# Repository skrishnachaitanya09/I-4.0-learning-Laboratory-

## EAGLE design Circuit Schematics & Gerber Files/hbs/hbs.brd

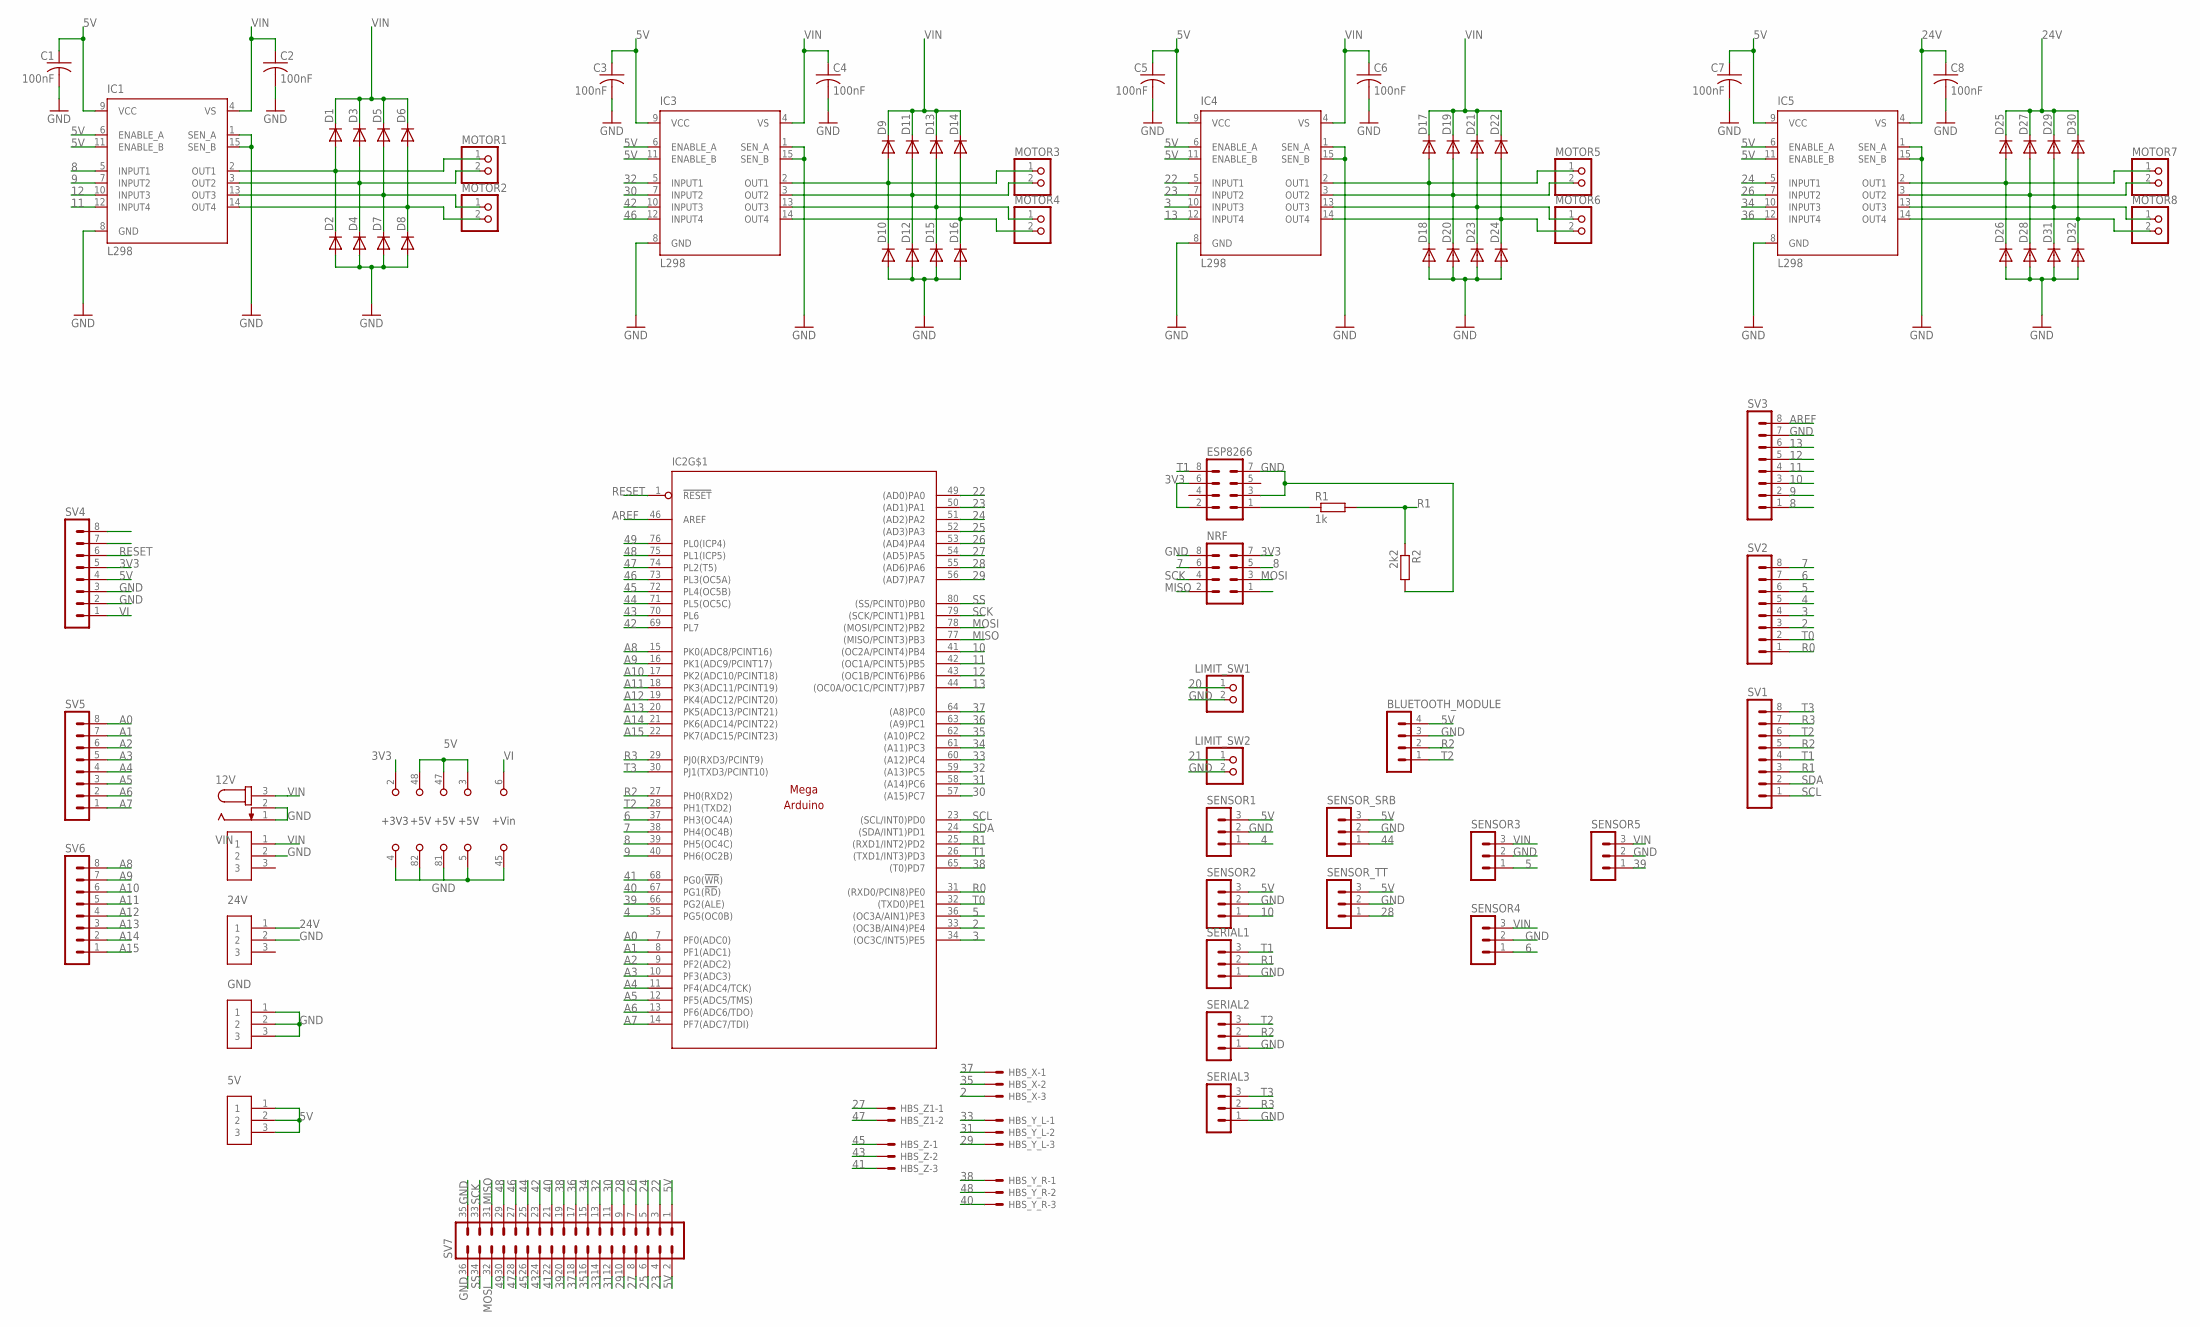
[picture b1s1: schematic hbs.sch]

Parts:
5V, 24V: 691311500003; TERMINALBLOCK_PLUGGABLE-3-5.08MM
12V: JACK-PLUG0; SPC4077
BLUETOOTH_MODULE: MA04-1
C1, C2, C3, C4, C5, C6, C7, C8: 100nF; C050-024X044
D1, D2, D3, D4, D5, D6, D7, D8, D9, D10, D11, D12, D13, D14, D15, D16, D17, D18, D19, D20, D21, D22, D23, D24, D25, D26, D27, D28, D29, D30, D31, D32: DIODE-D-5; D-5
ESP8266: MA04-2
GND: 691311500003; TERMINALBLOCK_PLUGGABLE-3-5.08MM
HBS_X: JST-XH-03-PIN-LONG-PAD; JST-XH-03-PACKAGE-LONG-PAD
HBS_Y_L: JST-XH-03-PIN-LONG-PAD; JST-XH-03-PACKAGE-LONG-PAD
HBS_Y_R: JST-XH-03-PIN-LONG-PAD; JST-XH-03-PACKAGE-LONG-PAD
HBS_Z: JST-XH-03-PIN-LONG-PAD; JST-XH-03-PACKAGE-LONG-PAD
HBS_Z1: JST-XH-02-PIN-LONG-PAD; JST-XH-02-PACKAGE-LONG-PAD
IC1, IC3, IC4, IC5: L298; MULTIWATT-15
IC2: MEGAARDUINO_21; MEGA_ARDUINO_1
LIMIT_SW1, LIMIT_SW2: PINHD-1X2; 1X02
MOTOR1, MOTOR2, MOTOR3, MOTOR4, MOTOR5, MOTOR6, MOTOR7, MOTOR8: PINHD-1X2; 1X02
NRF: MA04-2
R1: 1k; 0204/7
R2: 2k2; 0204/7
SENSOR1, SENSOR2, SENSOR3, SENSOR4, SENSOR5: MA03-1
SENSOR_SRB: MA03-1
SENSOR_TT: MA03-1
SERIAL1, SERIAL2, SERIAL3: MA03-1
SV1, SV2, SV3, SV4, SV5, SV6: MA08-1
SV7: MA18-2
VIN: 691311500003; TERMINALBLOCK_PLUGGABLE-3-5.08MM

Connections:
2: HBS_X.3, IC2.33 ((OC3B/AIN4)PE4), SV2.3
3: IC2.34 ((OC3C/INT5)PE5), IC4.10 (INPUT3), SV2.4
3V3: ESP8266.2, ESP8266.6, IC2.2 (+3V3), NRF.7, SV4.5
4: IC2.35 (PG5(OC0B)), SENSOR1.1, SV2.5
5: IC2.36 ((OC3A/AIN1)PE3), SENSOR3.1, SV2.6
5V: 5V.1, 5V.2, 5V.3, BLUETOOTH_MODULE.4, C1.1, C3.1, C5.1, C7.1, IC1.6 (ENABLE_A), IC1.9 (VCC), IC1.11 (ENABLE_B), IC2.3 (+5V), IC2.47 (+5V), IC2.48 (+5V), IC3.6 (ENABLE_A), IC3.9 (VCC), IC3.11 (ENABLE_B), IC4.6 (ENABLE_A), IC4.9 (VCC), IC4.11 (ENABLE_B), IC5.6 (ENABLE_A), IC5.9 (VCC), IC5.11 (ENABLE_B), SENSOR1.3, SENSOR2.3, SENSOR_SRB.3, SENSOR_TT.3, SV4.4, SV7.1, SV7.2
6: IC2.37 (PH3(OC4A)), SENSOR4.1, SV2.7
7: IC2.38 (PH4(OC4B)), NRF.6, SV2.8
8: IC1.5 (INPUT1), IC2.39 (PH5(OC4C)), NRF.5, SV3.1
9: IC1.7 (INPUT2), IC2.40 (PH6(OC2B)), SV3.2
10: IC2.41 ((OC2A/PCINT4)PB4), SENSOR2.1, SV3.3
11: IC1.12 (INPUT4), IC2.42 ((OC1A/PCINT5)PB5), SV3.4
12: IC1.10 (INPUT3), IC2.43 ((OC1B/PCINT6)PB6), SV3.5
13: IC2.44 ((OC0A/OC1C/PCINT7)PB7), IC4.12 (INPUT4), SV3.6
20: LIMIT_SW1.1
21: LIMIT_SW2.1
22: IC2.49 ((AD0)PA0), IC4.5 (INPUT1), SV7.3
23: IC2.50 ((AD1)PA1), IC4.7 (INPUT2), SV7.4
24: IC2.51 ((AD2)PA2), IC5.5 (INPUT1), SV7.5
24V: 24V.1, C8.1, D25.C, D27.C, D29.C, D30.C, IC5.4 (VS)
25: IC2.52 ((AD3)PA3), SV7.6
26: IC2.53 ((AD4)PA4), IC5.7 (INPUT2), SV7.7
27: HBS_Z1.1, IC2.54 ((AD5)PA5), SV7.8
28: IC2.55 ((AD6)PA6), SENSOR_TT.1, SV7.9
29: HBS_Y_L.3, IC2.56 ((AD7)PA7), SV7.10
30: IC2.57 ((A15)PC7), IC3.7 (INPUT2), SV7.11
31: HBS_Y_L.2, IC2.58 ((A14)PC6), SV7.12
32: IC2.59 ((A13)PC5), IC3.5 (INPUT1), SV7.13
33: HBS_Y_L.1, IC2.60 ((A12)PC4), SV7.14
34: IC2.61 ((A11)PC3), IC5.10 (INPUT3), SV7.15
35: HBS_X.2, IC2.62 ((A10)PC2), SV7.16
36: IC2.63 ((A9)PC1), IC5.12 (INPUT4), SV7.17
37: HBS_X.1, IC2.64 ((A8)PC0), SV7.18
38: HBS_Y_R.1, IC2.65 ((T0)PD7), SV7.19
39: IC2.66 (PG2(ALE)), SENSOR5.1, SV7.20
40: HBS_Y_R.3, IC2.67 (PG1(!RD!)), SV7.21
41: HBS_Z.3, IC2.68 (PG0(!WR!)), SV7.22
42: IC2.69 (PL7), IC3.10 (INPUT3), SV7.23
43: HBS_Z.2, IC2.70 (PL6), SV7.24
44: IC2.71 (PL5(OC5C)), SENSOR_SRB.1, SV7.25
45: HBS_Z.1, IC2.72 (PL4(OC5B)), SV7.26
46: IC2.73 (PL3(OC5A)), IC3.12 (INPUT4), SV7.27
47: HBS_Z1.2, IC2.74 (PL2(T5)), SV7.28
48: HBS_Y_R.2, IC2.75 (PL1(ICP5)), SV7.29
49: IC2.76 (PL0(ICP4)), SV7.30
A0: IC2.7 (PF0(ADC0)), SV5.8
A1: IC2.8 (PF1(ADC1)), SV5.7
A2: IC2.9 (PF2(ADC2)), SV5.6
A3: IC2.10 (PF3(ADC3)), SV5.5
A4: IC2.11 (PF4(ADC4/TCK)), SV5.4
A5: IC2.12 (PF5(ADC5/TMS)), SV5.3
A6: IC2.13 (PF6(ADC6/TDO)), SV5.2
A7: IC2.14 (PF7(ADC7/TDI)), SV5.1
A8: IC2.15 (PK0(ADC8/PCINT16)), SV6.8
A9: IC2.16 (PK1(ADC9/PCINT17)), SV6.7
A10: IC2.17 (PK2(ADC10/PCINT18)), SV6.6
A11: IC2.18 (PK3(ADC11/PCINT19)), SV6.5
A12: IC2.19 (PK4(ADC12/PCINT20)), SV6.4
A13: IC2.20 (PK5(ADC13/PCINT21)), SV6.3
A14: IC2.21 (PK6(ADC14/PCINT22)), SV6.2
A15: IC2.22 (PK7(ADC15/PCINT23)), SV6.1
AREF: IC2.46 (AREF), SV3.8
GND: 12V.1, 12V.2, 24V.2, BLUETOOTH_MODULE.3, C1.2, C2.2, C3.2, C4.2, C5.2, C6.2, C7.2, C8.2, D2.A, D4.A, D7.A, D8.A, D10.A, D12.A, D15.A, D16.A, D18.A, D20.A, D23.A, D24.A, D26.A, D28.A, D31.A, D32.A, ESP8266.3, ESP8266.7, GND.1, GND.2, GND.3, IC1.1 (SEN_A), IC1.8 (GND), IC1.15 (SEN_B), IC2.4 (GND), IC2.5 (GND), IC2.45 (GND), IC2.81 (GND), IC2.82 (GND), IC3.1 (SEN_A), IC3.8 (GND), IC3.15 (SEN_B), IC4.1 (SEN_A), IC4.8 (GND), IC4.15 (SEN_B), IC5.1 (SEN_A), IC5.8 (GND), IC5.15 (SEN_B), LIMIT_SW1.2, LIMIT_SW2.2, NRF.8, R2.2, SENSOR1.2, SENSOR2.2, SENSOR3.2, SENSOR4.2, SENSOR5.2, SENSOR_SRB.2, SENSOR_TT.2, SERIAL1.1, SERIAL2.1, SERIAL3.1, SV3.7, SV4.2, SV4.3, SV7.35, SV7.36, VIN.2
MISO: IC2.77 ((MISO/PCINT3)PB3), NRF.2, SV7.31
MOSI: IC2.78 ((MOSI/PCINT2)PB2), NRF.3, SV7.32
unnamed: D1.A, D2.C, IC1.2 (OUT1), MOTOR1.1
unnamed: D3.A, D4.C, IC1.3 (OUT2), MOTOR1.2
unnamed: D6.A, D8.C, IC1.14 (OUT4), MOTOR2.2
unnamed: D5.A, D7.C, IC1.13 (OUT3), MOTOR2.1
unnamed: ESP8266.1, R1.1
unnamed: D9.A, D10.C, IC3.2 (OUT1), MOTOR3.1
unnamed: D11.A, D12.C, IC3.3 (OUT2), MOTOR3.2
unnamed: D14.A, D16.C, IC3.14 (OUT4), MOTOR4.2
unnamed: D13.A, D15.C, IC3.13 (OUT3), MOTOR4.1
unnamed: D17.A, D18.C, IC4.2 (OUT1), MOTOR5.1
unnamed: D19.A, D20.C, IC4.3 (OUT2), MOTOR5.2
unnamed: D22.A, D24.C, IC4.14 (OUT4), MOTOR6.2
unnamed: D21.A, D23.C, IC4.13 (OUT3), MOTOR6.1
unnamed: D25.A, D26.C, IC5.2 (OUT1), MOTOR7.1
unnamed: D27.A, D28.C, IC5.3 (OUT2), MOTOR7.2
unnamed: D30.A, D32.C, IC5.14 (OUT4), MOTOR8.2
unnamed: D29.A, D31.C, IC5.13 (OUT3), MOTOR8.1
R0: IC2.31 ((RXD0/PCIN8)PE0), SV2.1
R1: IC2.25 ((RXD1/INT2)PD2), R1.2, R2.1, SERIAL1.2, SV1.3
R2: BLUETOOTH_MODULE.2, IC2.27 (PH0(RXD2)), SERIAL2.2, SV1.5
R3: IC2.29 (PJ0(RXD3/PCINT9)), SERIAL3.2, SV1.7
RESET: IC2.1 (!RESET), SV4.6
SCK: IC2.79 ((SCK/PCINT1)PB1), NRF.4, SV7.33
SCL: IC2.23 ((SCL/INT0)PD0), SV1.1
SDA: IC2.24 ((SDA/INT1)PD1), SV1.2
SS: IC2.80 ((SS/PCINT0)PB0), SV7.34
T0: IC2.32 ((TXD0)PE1), SV2.2
T1: ESP8266.8, IC2.26 ((TXD1/INT3)PD3), SERIAL1.3, SV1.4
T2: BLUETOOTH_MODULE.1, IC2.28 (PH1(TXD2)), SERIAL2.3, SV1.6
T3: IC2.30 (PJ1(TXD3/PCINT10)), SERIAL3.3, SV1.8
VI: IC2.6 (+VIN), SV4.1
VIN: 12V.3, C2.1, C4.1, C6.1, D1.C, D3.C, D5.C, D6.C, D9.C, D11.C, D13.C, D14.C, D17.C, D19.C, D21.C, D22.C, IC1.4 (VS), IC3.4 (VS), IC4.4 (VS), SENSOR3.3, SENSOR4.3, SENSOR5.3, VIN.1

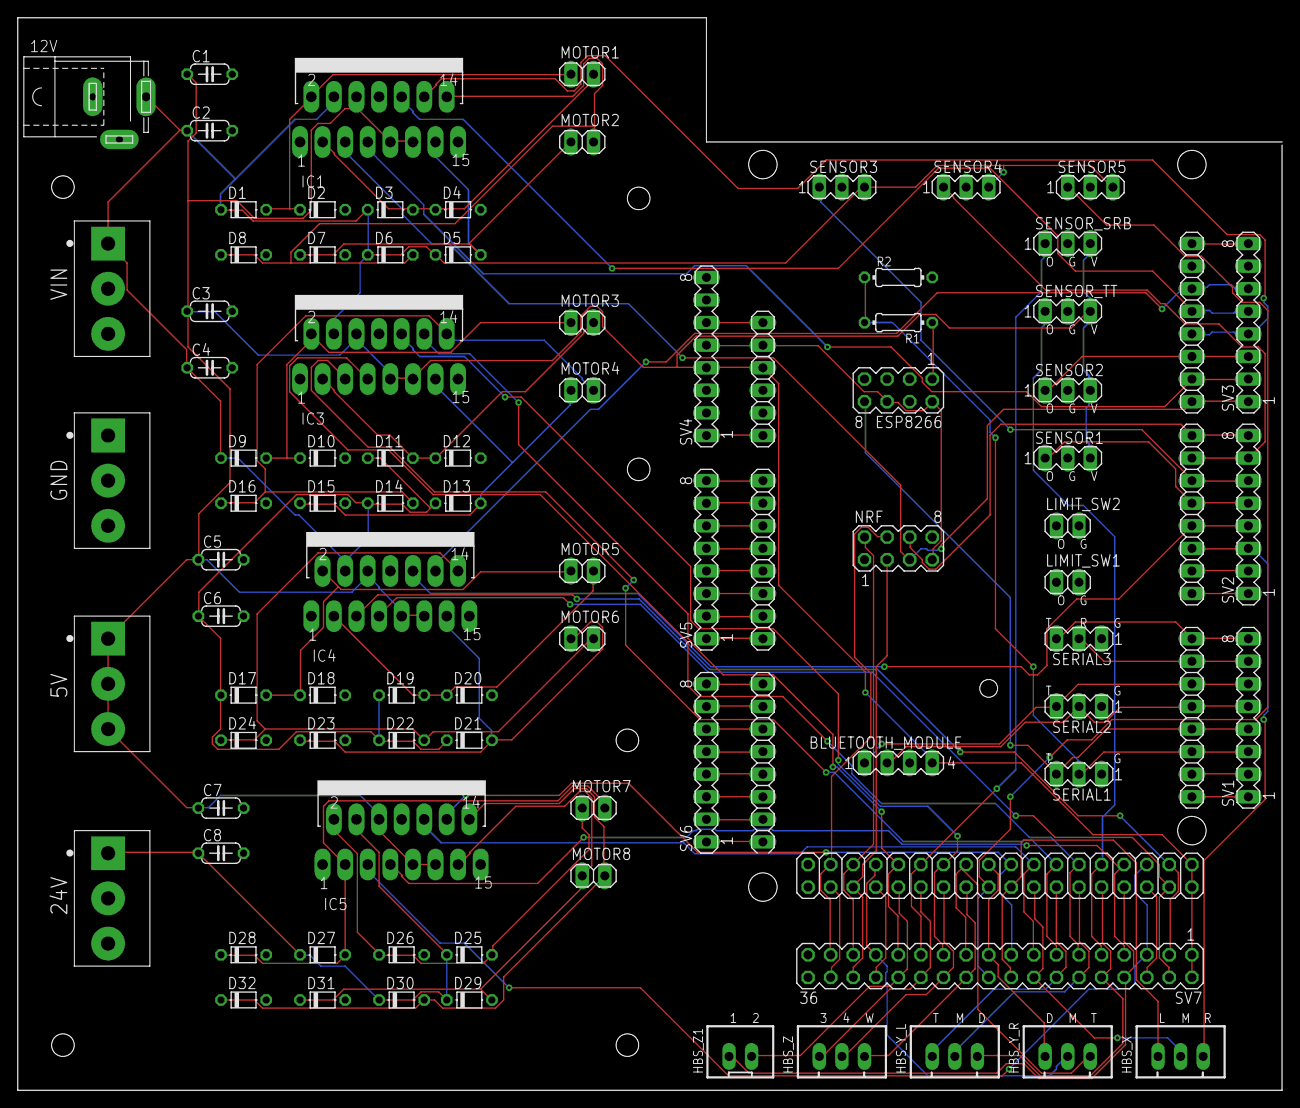
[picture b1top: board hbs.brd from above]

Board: 2 copper layers, 142.2 x 120.7 mm, 87 parts (0 on the bottom side), 95 nets.

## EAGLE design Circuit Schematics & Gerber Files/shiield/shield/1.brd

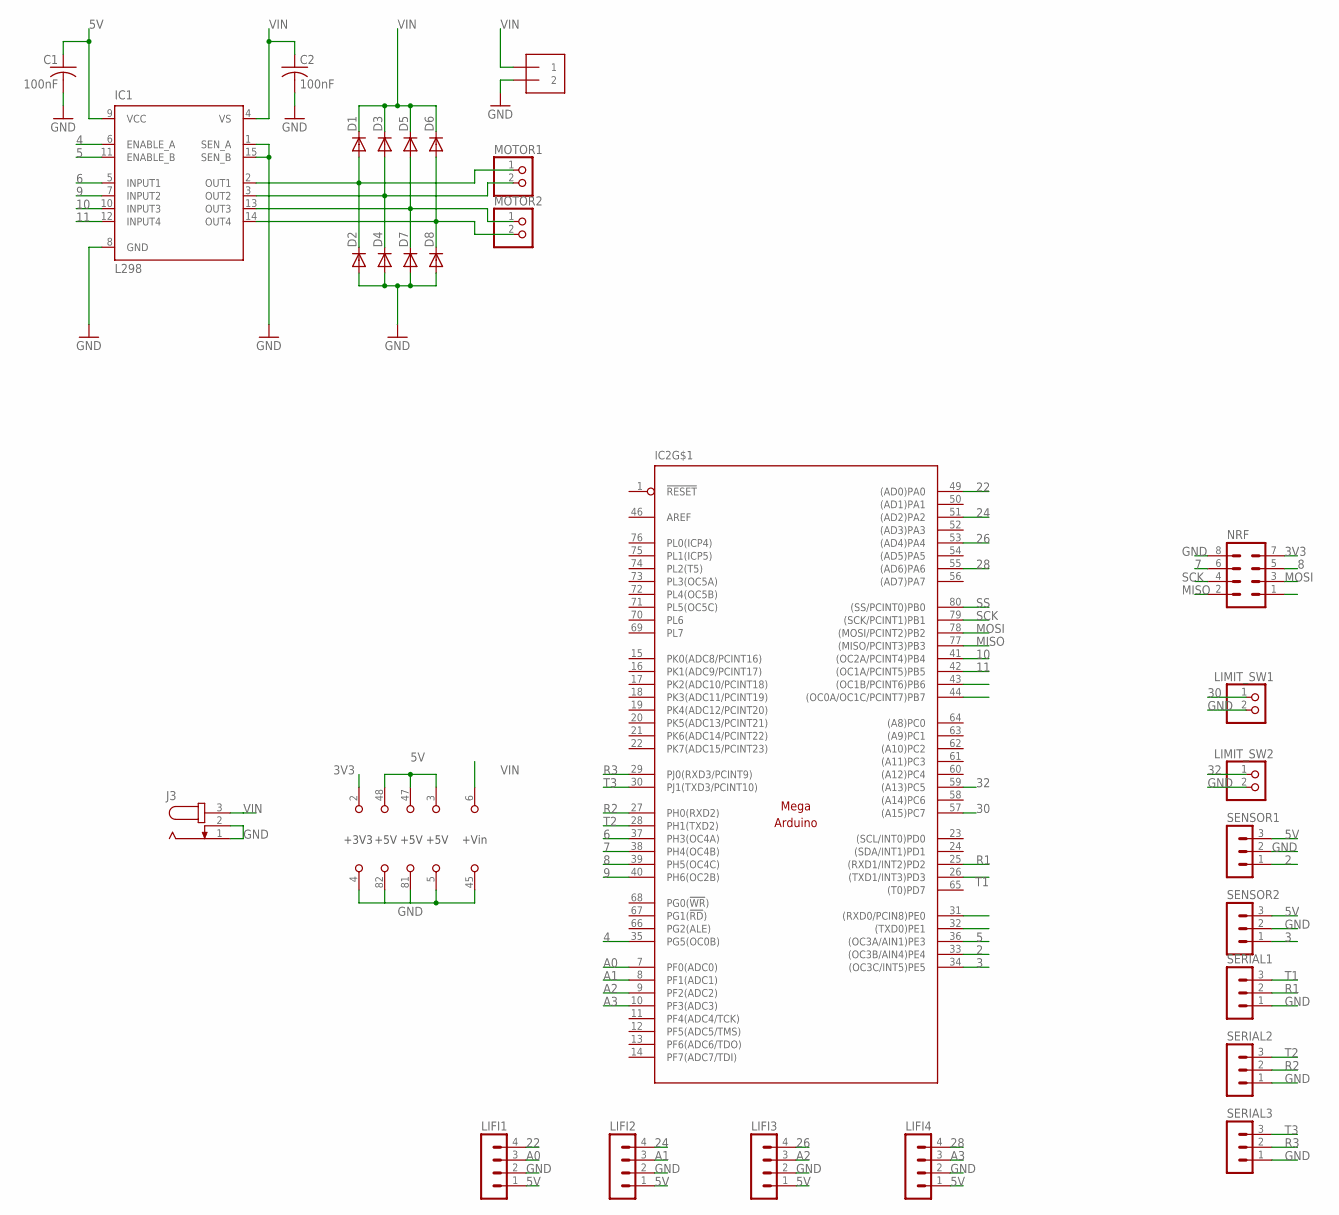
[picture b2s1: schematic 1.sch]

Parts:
C1, C2: 100nF; C050-024X044
D1, D2, D3, D4, D5, D6, D7, D8: DIODE-D-5; D-5
IC1: L298; MULTIWATT-15
IC2: MEGAARDUINO_21; MEGA_ARDUINO_1
J1: 1X2-3.5MM
J3: JACK-PLUG0; SPC4077
LIFI1, LIFI2, LIFI3, LIFI4: MA04-1
LIMIT_SW1, LIMIT_SW2: PINHD-1X2; 1X02
MOTOR1, MOTOR2: PINHD-1X2; 1X02
NRF: MA04-2
SENSOR1, SENSOR2: MA03-1
SERIAL1, SERIAL2, SERIAL3: MA03-1

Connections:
2: IC2.33 ((OC3B/AIN4)PE4), SENSOR1.1
3: IC2.34 ((OC3C/INT5)PE5), SENSOR2.1
3V3: IC2.2 (+3V3), NRF.7
4: IC1.6 (ENABLE_A), IC2.35 (PG5(OC0B))
5: IC1.11 (ENABLE_B), IC2.36 ((OC3A/AIN1)PE3)
5V: C1.1, IC1.9 (VCC), IC2.3 (+5V), IC2.47 (+5V), IC2.48 (+5V), LIFI1.1, LIFI2.1, LIFI3.1, LIFI4.1, SENSOR1.3, SENSOR2.3
6: IC1.5 (INPUT1), IC2.37 (PH3(OC4A))
7: IC2.38 (PH4(OC4B)), NRF.6
8: IC2.39 (PH5(OC4C)), NRF.5
9: IC1.7 (INPUT2), IC2.40 (PH6(OC2B))
10: IC1.10 (INPUT3), IC2.41 ((OC2A/PCINT4)PB4)
11: IC1.12 (INPUT4), IC2.42 ((OC1A/PCINT5)PB5)
22: IC2.49 ((AD0)PA0), LIFI1.4
24: IC2.51 ((AD2)PA2), LIFI2.4
26: IC2.53 ((AD4)PA4), LIFI3.4
28: IC2.55 ((AD6)PA6), LIFI4.4
30: IC2.57 ((A15)PC7), LIMIT_SW1.1
32: IC2.59 ((A13)PC5), LIMIT_SW2.1
A0: IC2.7 (PF0(ADC0)), LIFI1.3
A1: IC2.8 (PF1(ADC1)), LIFI2.3
A2: IC2.9 (PF2(ADC2)), LIFI3.3
A3: IC2.10 (PF3(ADC3)), LIFI4.3
GND: C1.2, C2.2, D2.A, D4.A, D7.A, D8.A, IC1.1 (SEN_A), IC1.8 (GND), IC1.15 (SEN_B), IC2.4 (GND), IC2.5 (GND), IC2.45 (GND), IC2.81 (GND), IC2.82 (GND), J1.2, J3.1, J3.2, LIFI1.2, LIFI2.2, LIFI3.2, LIFI4.2, LIMIT_SW1.2, LIMIT_SW2.2, NRF.8, SENSOR1.2, SENSOR2.2, SERIAL1.1, SERIAL2.1, SERIAL3.1
MISO: IC2.77 ((MISO/PCINT3)PB3), NRF.2
MOSI: IC2.78 ((MOSI/PCINT2)PB2), NRF.3
unnamed: D1.A, D2.C, IC1.2 (OUT1), MOTOR1.1
unnamed: D3.A, D4.C, IC1.3 (OUT2), MOTOR1.2
unnamed: D6.A, D8.C, IC1.14 (OUT4), MOTOR2.2
unnamed: D5.A, D7.C, IC1.13 (OUT3), MOTOR2.1
R1: IC2.25 ((RXD1/INT2)PD2), SERIAL1.2
R2: IC2.27 (PH0(RXD2)), SERIAL2.2
R3: IC2.29 (PJ0(RXD3/PCINT9)), SERIAL3.2
SCK: IC2.79 ((SCK/PCINT1)PB1), NRF.4
SS: IC2.80 ((SS/PCINT0)PB0)
T1: IC2.26 ((TXD1/INT3)PD3), SERIAL1.3
T2: IC2.28 (PH1(TXD2)), SERIAL2.3
T3: IC2.30 (PJ1(TXD3/PCINT10)), SERIAL3.3
VIN: C2.1, D1.C, D3.C, D5.C, D6.C, IC1.4 (VS), IC2.6 (+VIN), J1.1, J3.3

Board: 2 copper layers, 28 parts (0 on the bottom side), 37 nets, no tracks yet.

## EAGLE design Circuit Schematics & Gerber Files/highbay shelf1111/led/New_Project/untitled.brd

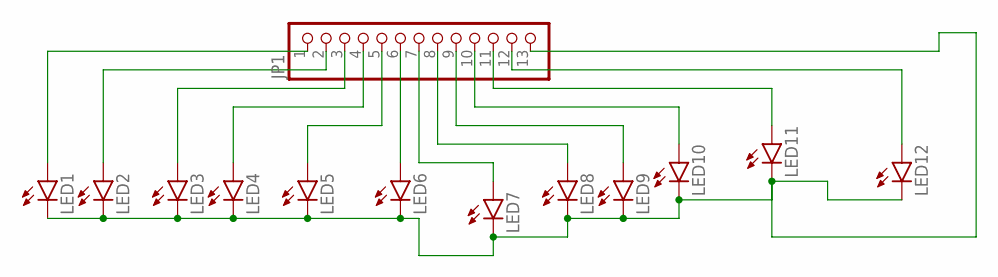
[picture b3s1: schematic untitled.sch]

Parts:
JP1: PINHD-1X13; 1X13
LED1, LED2, LED3, LED4, LED5, LED6, LED7, LED8, LED9, LED10, LED11, LED12: LED5MM

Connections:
unnamed: JP1.1, LED1.A
unnamed: JP1.2, LED2.A
unnamed: JP1.3, LED3.A
unnamed: JP1.4, LED4.A
unnamed: JP1.5, LED5.A
unnamed: JP1.6, LED6.A
unnamed: JP1.7, LED7.A
unnamed: JP1.8, LED8.A
unnamed: JP1.9, LED9.A
unnamed: JP1.10, LED10.A
unnamed: JP1.11, LED11.A
unnamed: JP1.12, LED12.A
unnamed: JP1.13, LED1.K (C), LED2.K (C), LED3.K (C), LED4.K (C), LED5.K (C), LED6.K (C), LED7.K (C), LED8.K (C), LED9.K (C), LED10.K (C), LED11.K (C), LED12.K (C)

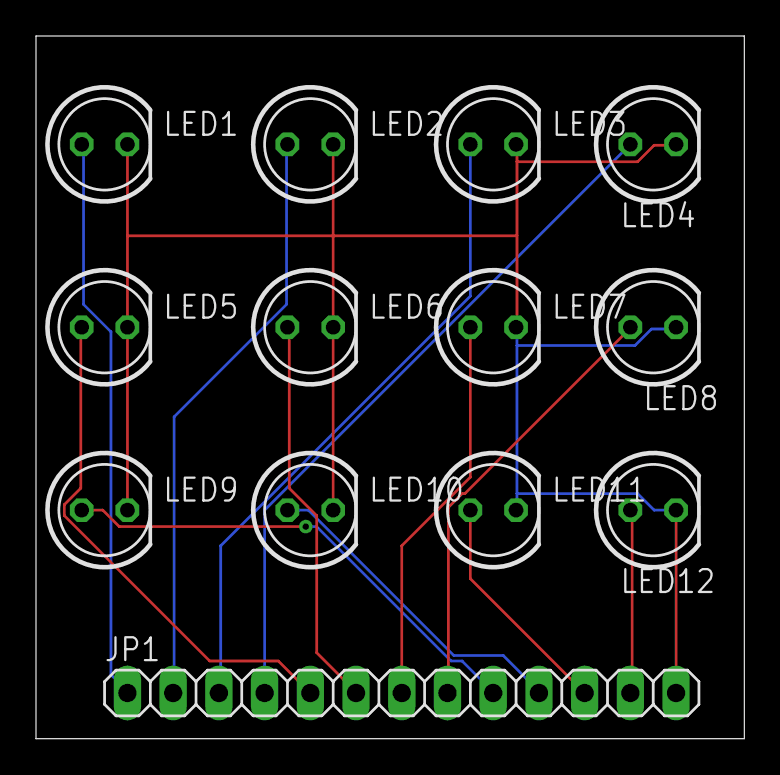
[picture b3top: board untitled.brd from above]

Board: 2 copper layers, 39.4 x 39.0 mm, 13 parts (0 on the bottom side), 13 nets.

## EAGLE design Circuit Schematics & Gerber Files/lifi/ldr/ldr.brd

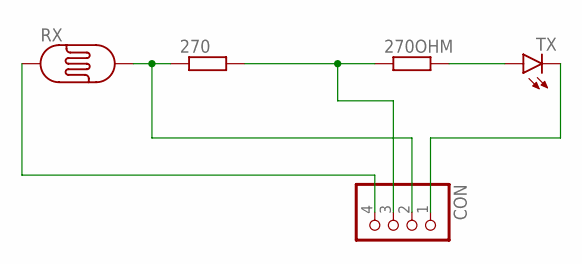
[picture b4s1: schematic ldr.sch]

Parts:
270, 270OHM: R-EU_0207/7; 0207/7
CON: PINHD-1X4; 1X04
RX: PHOTOCELLONB; ON_BOARD
TX: LED5MM

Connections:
unnamed: 270.1, CON.2, RX.2
unnamed: 270.2, 270OHM.1, CON.3
unnamed: 270OHM.2, TX.A
unnamed: CON.4, RX.1
unnamed: CON.1, TX.K (C)

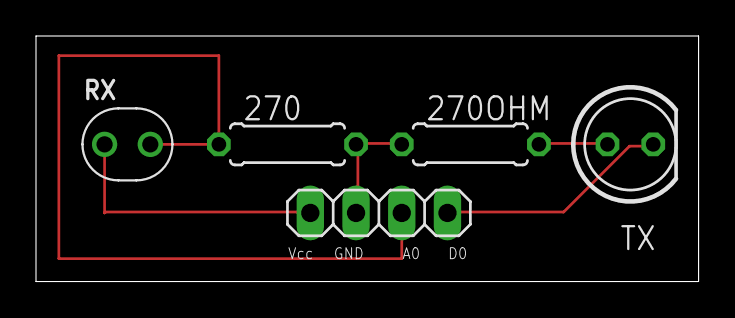
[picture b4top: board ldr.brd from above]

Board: 2 copper layers, 36.8 x 13.6 mm, 5 parts (0 on the bottom side), 5 nets.

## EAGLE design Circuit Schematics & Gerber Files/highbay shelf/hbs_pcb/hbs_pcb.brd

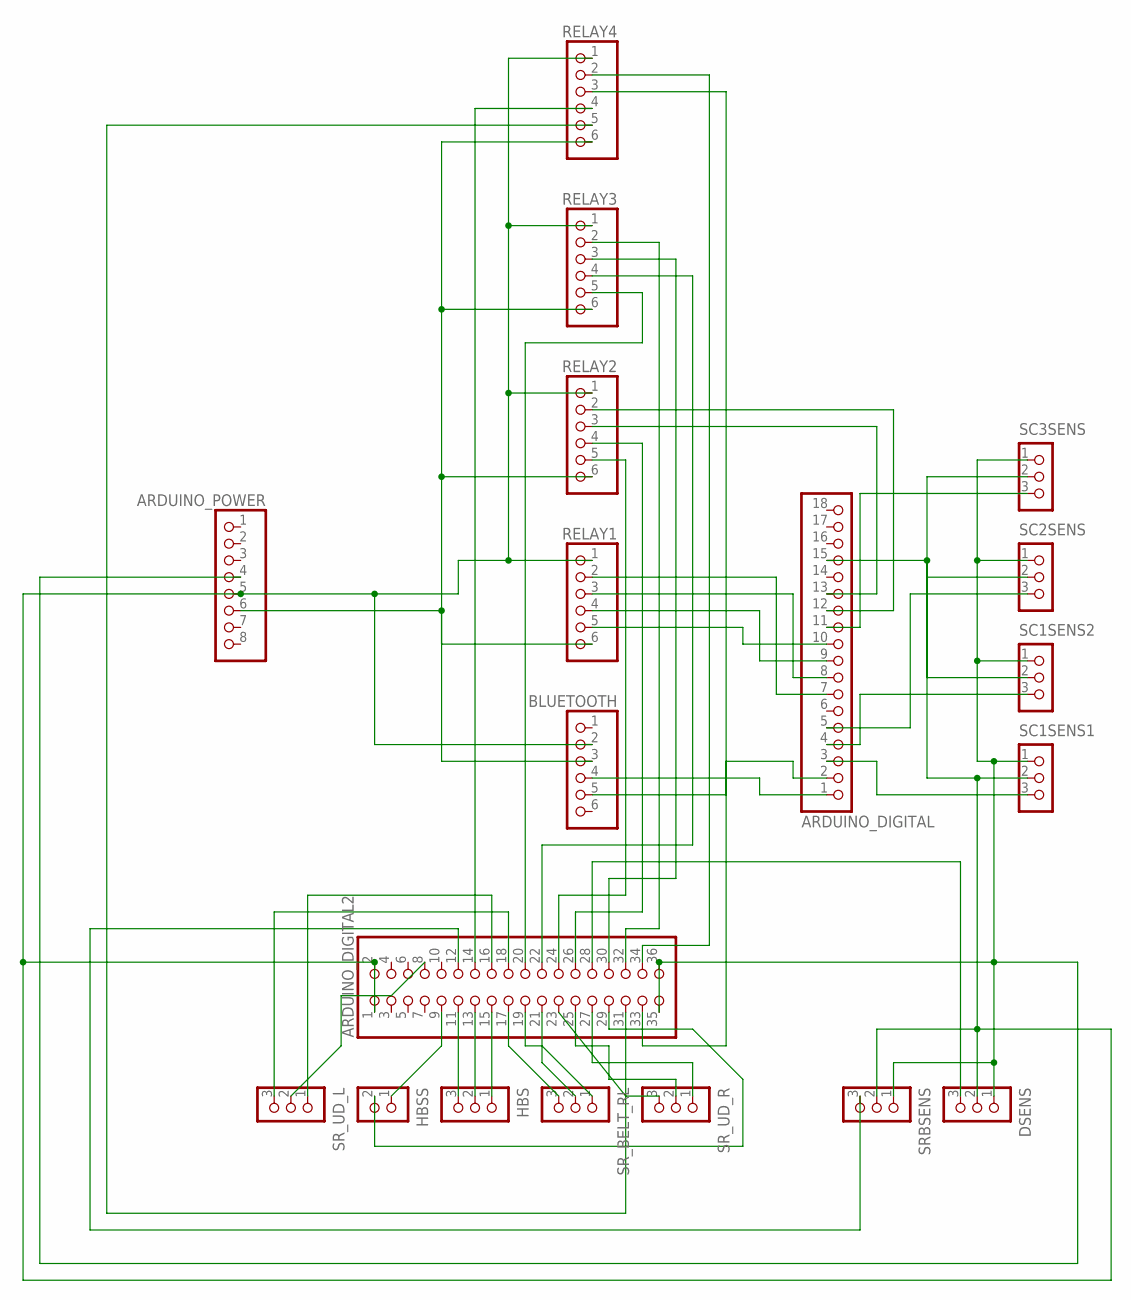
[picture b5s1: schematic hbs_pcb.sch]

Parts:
ARDUINO_DIGITAL: PINHD-1X18; 1X18
ARDUINO_DIGITAL2: PINHD-2X18; 2X18
ARDUINO_POWER: PINHD-1X8; 1X08
BLUETOOTH: PINHD-1X6; 1X06
DSENS: CON_TERMINAL_BLOCK_03-5MM; TERMINAL_BLOCK_3P_5
HBS: CON_TERMINAL_BLOCK_03-5MM; TERMINAL_BLOCK_3P_5
HBSS: CON_TERMINAL_BLOCK_02-5MM; TERMINAL_BLOCK_2P_5
RELAY1, RELAY2, RELAY3, RELAY4: PINHD-1X6; 1X06
SC1SENS1, SC1SENS2, SC2SENS, SC3SENS: CON_TERMINAL_BLOCK_03-5MM; TERMINAL_BLOCK_3P_5
SRBSENS: CON_TERMINAL_BLOCK_03-5MM; TERMINAL_BLOCK_3P_5
SR_BELT_RL: CON_TERMINAL_BLOCK_03-5MM; TERMINAL_BLOCK_3P_5
SR_UD_L: CON_TERMINAL_BLOCK_03-5MM; TERMINAL_BLOCK_3P_5
SR_UD_R: CON_TERMINAL_BLOCK_03-5MM; TERMINAL_BLOCK_3P_5

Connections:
unnamed: ARDUINO_DIGITAL.1, BLUETOOTH.4
unnamed: ARDUINO_DIGITAL.2, BLUETOOTH.5
unnamed: ARDUINO_DIGITAL.3, SC1SENS1.3
unnamed: ARDUINO_DIGITAL.4, SC1SENS2.3
unnamed: ARDUINO_DIGITAL.5, SC2SENS.3
unnamed: ARDUINO_DIGITAL.11, SC3SENS.3
unnamed: ARDUINO_DIGITAL.7, RELAY1.2
unnamed: ARDUINO_DIGITAL.8, RELAY1.3
unnamed: ARDUINO_DIGITAL.9, RELAY1.4
unnamed: ARDUINO_DIGITAL.10, RELAY1.5
unnamed: ARDUINO_DIGITAL.12, RELAY2.2
unnamed: ARDUINO_DIGITAL.13, RELAY2.3
unnamed: ARDUINO_DIGITAL2.26, RELAY2.4
unnamed: ARDUINO_DIGITAL2.24, RELAY2.5
unnamed: ARDUINO_DIGITAL2.32, RELAY3.2
unnamed: ARDUINO_DIGITAL2.30, RELAY3.3
unnamed: ARDUINO_DIGITAL2.28, DSENS.3
unnamed: ARDUINO_DIGITAL2.22, RELAY3.4
unnamed: ARDUINO_DIGITAL2.20, RELAY3.5
unnamed: ARDUINO_DIGITAL2.34, RELAY4.2
unnamed: ARDUINO_DIGITAL2.33, RELAY4.3
unnamed: ARDUINO_DIGITAL2.14, RELAY4.4
unnamed: ARDUINO_DIGITAL2.31, RELAY4.5
unnamed: ARDUINO_POWER.6, BLUETOOTH.3, RELAY1.6, RELAY2.6, RELAY3.6, RELAY4.6
unnamed: ARDUINO_DIGITAL2.12, SRBSENS.3
unnamed: ARDUINO_DIGITAL2.27, SR_UD_R.1
unnamed: ARDUINO_DIGITAL2.25, SR_UD_R.2
unnamed: ARDUINO_DIGITAL2.23, SR_UD_R.3
unnamed: ARDUINO_DIGITAL2.21, SR_BELT_RL.2
unnamed: ARDUINO_DIGITAL2.19, SR_BELT_RL.1
unnamed: ARDUINO_DIGITAL2.17, SR_BELT_RL.3
unnamed: ARDUINO_DIGITAL2.15, HBS.1
unnamed: ARDUINO_DIGITAL2.13, HBS.2
unnamed: ARDUINO_DIGITAL2.11, HBS.3
unnamed: ARDUINO_DIGITAL2.9, HBSS.1
unnamed: ARDUINO_DIGITAL2.29, HBSS.2
unnamed: ARDUINO_DIGITAL2.8, SR_UD_L.2
unnamed: ARDUINO_DIGITAL2.18, SR_UD_L.3
unnamed: ARDUINO_DIGITAL2.16, SR_UD_L.1
unnamed: ARDUINO_DIGITAL2.35, ARDUINO_DIGITAL2.36, ARDUINO_POWER.4, DSENS.1, SC1SENS1.1, SC1SENS2.1, SC2SENS.1, SC3SENS.1, SRBSENS.1
unnamed: ARDUINO_DIGITAL.15, ARDUINO_DIGITAL2.1, ARDUINO_DIGITAL2.2, ARDUINO_POWER.5, BLUETOOTH.2, DSENS.2, RELAY1.1, RELAY2.1, RELAY3.1, RELAY4.1, SC1SENS1.2, SC1SENS2.2, SC2SENS.2, SC3SENS.2, SRBSENS.2

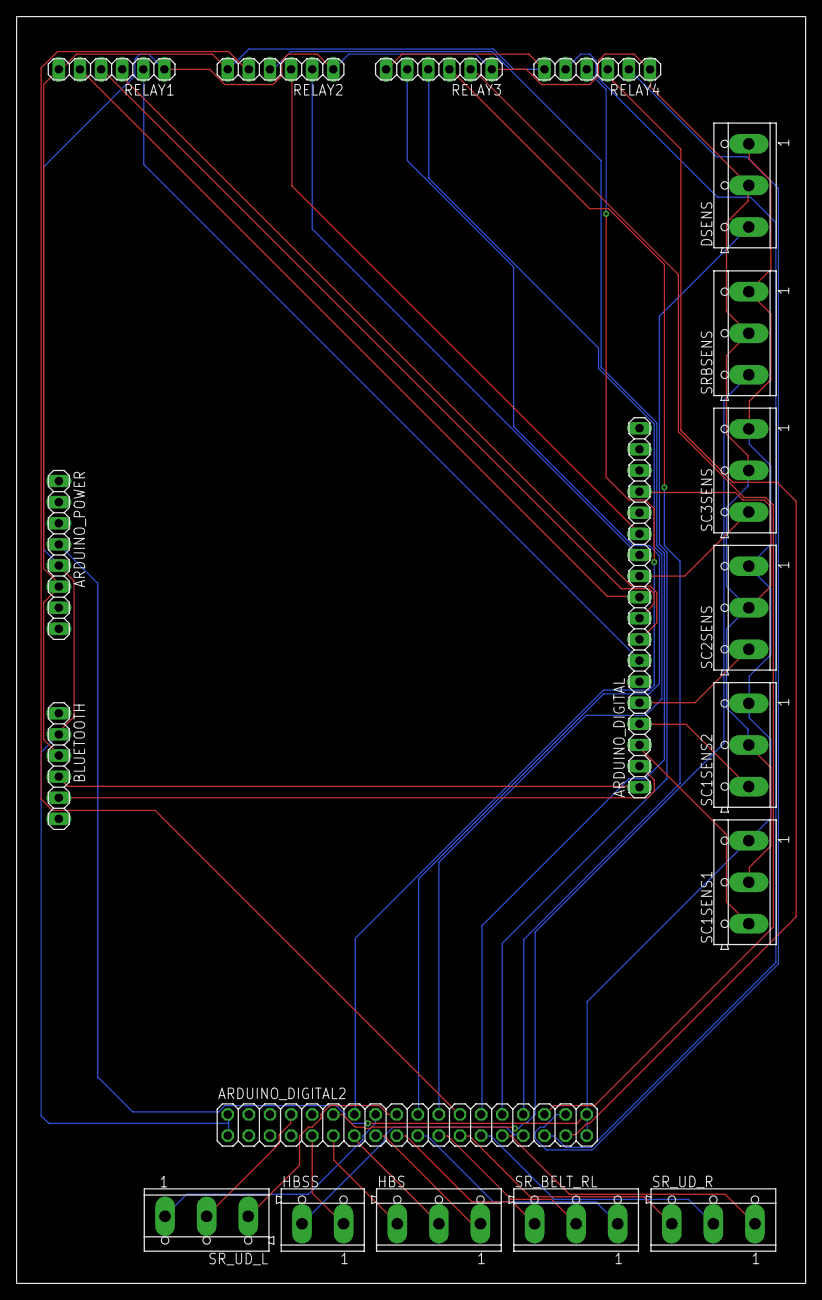
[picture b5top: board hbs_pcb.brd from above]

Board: 2 copper layers, 94.9 x 152.4 mm, 19 parts (0 on the bottom side), 41 nets.

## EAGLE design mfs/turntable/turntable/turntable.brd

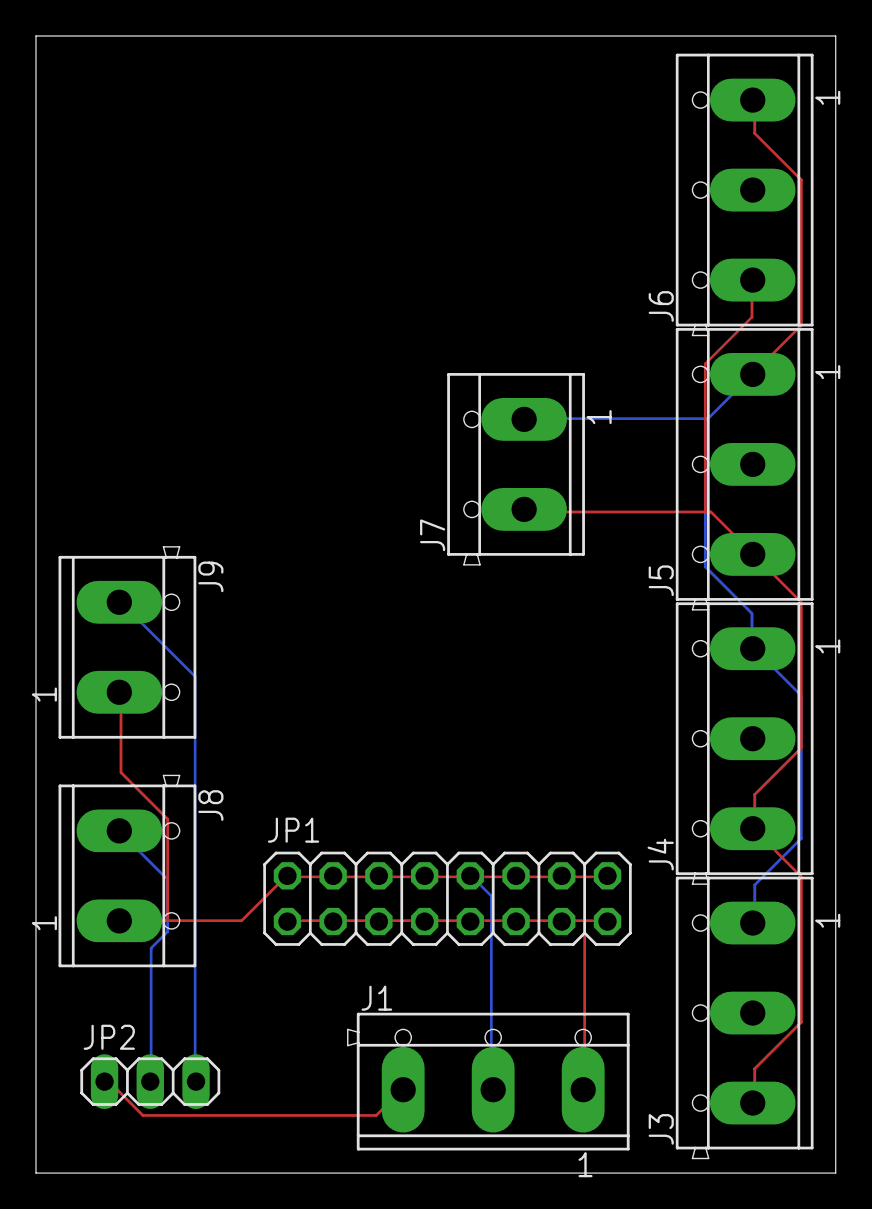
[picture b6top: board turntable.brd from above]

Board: 2 copper layers, 44.4 x 63.2 mm, 10 parts (0 on the bottom side), 7 nets.

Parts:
J1, J3, J4, J5, J6: CON_TERMINAL_BLOCK_03-5MM; TERMINAL_BLOCK_3P_5
J7, J8, J9: CON_TERMINAL_BLOCK_02-5MM; TERMINAL_BLOCK_2P_5
JP1: 2X08
JP2: 1X03

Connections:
unnamed: J1.1, JP1.1, JP1.3, JP1.5, JP1.7, JP1.9, JP1.11, JP1.13, JP1.15
unnamed: J1.2, J8.1, J9.1, JP1.2, JP1.4, JP1.6, JP1.8, JP1.10, JP1.12, JP1.14, JP1.16
unnamed: J1.3, JP2.1
unnamed: J8.2, JP2.2
unnamed: J3.1, J4.1, J5.1, J6.1, J7.1
unnamed: J9.2, JP2.3
unnamed: J3.3, J4.3, J5.3, J6.3, J7.2

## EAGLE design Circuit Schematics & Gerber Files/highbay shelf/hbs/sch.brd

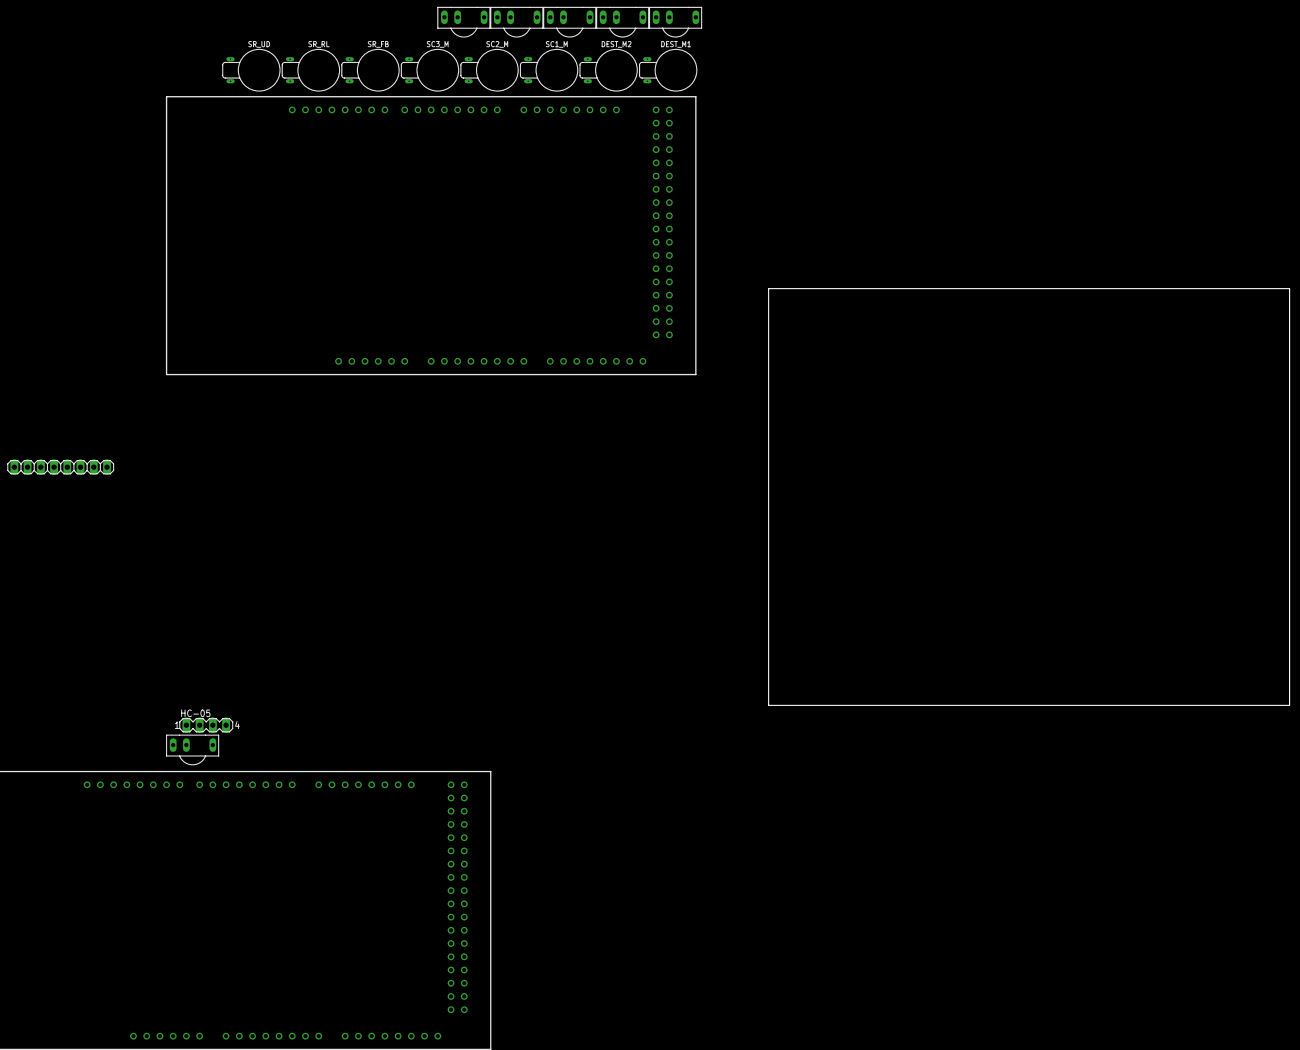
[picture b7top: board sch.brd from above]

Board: 2 copper layers, 100.0 x 80.0 mm, 18 parts (0 on the bottom side), 37 nets, no tracks yet.

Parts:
DEST_M1, DEST_M2: 308-100
HC-05: MA04-1
M1: RFID-RC522
SC1_M, SC2_M, SC3_M: 308-100
SC1_SENS1, SC1_SENS2, SC2_SENS, SC3_SENS: TSOP1730; TSOP17XX
SRB_SENS, SRB_SENS1: TSOP1730; TSOP17XX
SR_FB: 308-100
SR_RL: 308-100
SR_UD: 308-100
U$1, U$2: MEGA_DEVICE; MEGAOUTLINE

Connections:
unnamed: SC1_SENS1.OUT, U$1.2
unnamed: SC1_SENS2.OUT, U$1.3
unnamed: SC2_SENS.OUT, U$1.4
unnamed: SC3_SENS.OUT, U$1.10
unnamed: SRB_SENS.OUT, U$1.49
unnamed: HC-05.2, SC1_SENS1.V+, SC1_SENS2.V+, SC2_SENS.V+, SC3_SENS.V+, SRB_SENS.V+, SRB_SENS1.V+, U$1.5V
unnamed: HC-05.1, SC1_SENS1.GND, SC1_SENS2.GND, SC2_SENS.GND, SC3_SENS.GND, SRB_SENS.GND, SRB_SENS1.GND, U$1.GND@4
unnamed: SC1_M.POS, U$1.7
unnamed: SC1_M.NEG, U$1.6
unnamed: SC2_M.POS, U$1.9
unnamed: SC2_M.NEG, U$1.8
unnamed: SC3_M.POS, U$1.12
unnamed: SC3_M.NEG, U$1.11
unnamed: SR_UD.POS, U$1.26
unnamed: SR_UD.NEG, U$1.24
unnamed: SR_RL.NEG, U$1.20, U$1.30
unnamed: SR_FB.NEG, U$1.34
unnamed: SR_FB.POS, U$1.36
unnamed: DEST_M1.NEG, U$1.22
unnamed: DEST_M1.POS, U$1.23
unnamed: DEST_M2.NEG, U$1.25
unnamed: DEST_M2.POS, U$1.42
unnamed: U$1.18, U$2.19
unnamed: U$1.19, U$2.18
unnamed: U$1.17, U$2.16
unnamed: U$1.16, U$2.17
unnamed: U$1.GND@2, U$2.GND@4
unnamed: M1.3V3, U$2.RESET
unnamed: HC-05.4, U$1.1
unnamed: HC-05.3, U$1.0
unnamed: SRB_SENS1.OUT, U$1.28
unnamed: M1.RST, U$2.5
unnamed: M1.GND, U$2.GND@2
unnamed: M1.MISO, U$2.50
unnamed: M1.MOSI, U$2.51
unnamed: M1.SCK, U$2.52
unnamed: M1.SS, U$2.53

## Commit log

2020-03-05 Added Circuit schematics & Gerbers
2020-03-05 Test Codes Updated
2020-03-06 Added Robotic Arm test code
2020-03-09 Previous project reports
2020-03-09 conveyor test
2020-03-11 lifi test codes
2020-03-11 Device IDs added
2020-03-11 presentation
2020-03-11 lifi testcodes
2020-03-12 Version 1 Production Area
2020-03-13 lifi codes updates
2020-03-13 lifi test updated
2020-03-21 source conveyor updated
2020-07-22 highbay codes
    highbay codes
2020-08-19 highbay codes edited
2020-08-21 Added Presentation 2
2020-08-25 Added nrf test codes
2020-08-25 Added Production area RIOT LiFi codes
2020-08-27 Changed folders/files names
2020-08-31 Added conveyor nRF basic code
2020-09-04 Added dispatch conveyor nRF code
2020-09-07 Added Arm Test code
2020-09-07 Added slider test code
2020-09-07 pcb designs
2020-09-10 Updated dispatch conveyo coder
2020-10-08 pcb files updated
2020-10-27 Updated robotic arm code
2020-10-27 App for retrieving products(connected to firebase)
2020-11-02 Added IR and AGV codes
2020-11-05 Added robotic arm nrf code in Test codes
2020-11-18 Added HBS Test code
2020-11-18 Added Dispatch section final codes
2020-11-18 Replaced HBS Test code
2020-11-26 highbay pcb added
2020-12-08 Added High Bay Shelf final code
2020-12-09 Added Documentation for backup
2020-12-10 Added Documentation Files
2021-01-28 FinalCommit: Added AGV, RoboticArm and simulation files to FinalCodes
2021-01-28 Added HBS final code
2021-01-28 Moved old HBS codes to BasicTestCodes
2021-06-30 LiFi codes updated
2021-10-11 Updated HBS_Final_04102021 Code
